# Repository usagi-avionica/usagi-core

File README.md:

# Usagi Core

Flight computer core board by **Usagi Avionica**. An STM32G474 with on-board flash logging, CAN, USB-C and connectors for expansion boards, on a 50 × 50 mm four-layer board designed to be stacked.

## Features

- **MCU:** STM32G474RE (Arm Cortex-M4F, 170 MHz), 24 MHz crystal, 32.768 kHz RTC
- **Storage:** 256 Mbit (32 MB) SPI NOR flash (Infineon S25FL256L)
- **CAN:** classic CAN up to 1 Mbit/s (TI SN65HVD231Q), split termination on board, ESD protection
- **USB:** USB-C, ESD protected; can also power the board through a jumper for debug
- **Power:** 5 V input or USB into a 3.3 V / 1.2 A LDO
- **Expansion:** I2C, SPI, an 8-pin GPIO/ADC connector and 13 GPIO solder pads on the bottom side
- **Feedback:** buzzer, status LED, power indicator LEDs
- **Connectors:** Molex Micro-Lock Plus 1.25 mm with positive locks

## Specifications

| | |
|---|---|
| Board size | 50 × 50 mm |
| Mounting | 4 × M3, 3.5 mm from each corner (43 × 43 mm pattern) |
| Layers | 4, 1.6 mm, ENIG |
| Input voltage | 5 V nominal, **5.5 V maximum** |
| Logic level | 3.3 V |

## Connectors

All board-to-wire connectors are Molex Micro-Lock Plus 1.25 mm right-angle headers (220098 series). Mating housing: Molex 204532 series.

### J6: Power input

| Pin | Signal |
|---|---|
| 1 | VIN (5 V nominal, 5.5 V max) |
| 2 | GND |

### J3: CAN

| Pin | Signal |
|---|---|
| 1 | CANL |
| 2 | CANH |
| 3 | GND |

Split termination (2 × 60.4 Ω + 4.7 nF) is fitted on the board.

### J4: I2C (I2C3)

| Pin | Signal |
|---|---|
| 1 | SCL |
| 2 | SDA |
| 3 | GND |

1.8 kΩ pull-ups to 3.3 V on board.

### J5: SPI (SPI2)

| Pin | Signal |
|---|---|
| 1 | SCK |
| 2 | MISO |
| 3 | MOSI |
| 4 | GND |

There are no chip-select lines on this connector. Use pins from J7 or the solder pads for chip selects. Each SPI device should pull its own CS line up, so it stays deselected while the MCU is in reset.

### J2: Debug

| Pin | Signal |
|---|---|
| 1 | 3.3 V (VTref, reference only; does not power the board) |
| 2 | SWDIO |
| 3 | SWCLK |
| 4 | SWO |
| 5 | UART TX (USART2, from the MCU) |
| 6 | UART RX (USART2, to the MCU) |
| 7 | NRST |
| 8 | GND |

### J7: GPIO / ADC

| Pin | MCU pin | ADC channel |
|---|---|---|
| 1 | PC4 | ADC2_IN5 |
| 2 | PC5 | ADC2_IN11 |
| 3 | PC2 | ADC12_IN8 |
| 4 | PC1 | ADC12_IN7 |
| 5 | PC0 | ADC12_IN6 |
| 6 | PA8 | ADC5_IN1 |
| 7 | PB12 | ADC1_IN11 / ADC4_IN3 |
| 8 | PB11 | ADC12_IN14 |

Every pin can be a GPIO or an ADC input, and each uses a different EXTI line, so all eight can be interrupts at the same time. This connector has no ground pin; each daughter board takes its ground from its power or CAN connection.

> [!WARNING]
> J7 has **no ESD protection or filtering**. Keep signals between 0 and 3.3 V. In analog mode none of these pins are 5 V tolerant.

### GPIO solder pads (bottom side)

The remaining free GPIOs are on solder pads on the bottom of the board, labelled on the silkscreen:

PA10, PA15, PB4, PB7, PB9, PB10, PC6, PC7, PC10, PC11, PC12, PC13, PD2

These pads are unprotected and meant for development and bodge wires. Secure any wire that stays on in flight. PC13 can only source or sink a few mA, so use it only for slow signals.

### J1: USB-C

USB 2.0 full-speed device. It powers the board only when the USB EN jumper is fitted.

## Power

The board runs from J6 (5 V) or USB. The two are diode-ORed (Schottky) into a 3.3 V LDO, so both can be connected at once.

| Jumper | Function |
|---|---|
| USB EN | Fitted: USB powers the board. Removed: USB carries data only. |

| LED | Meaning |
|---|---|
| PWR IN | External power (J6) present |
| USB PWR | USB power present (J21 fitted) |
| 3.3V | 3.3 V rail on |
| STATE | Status LED, driven by firmware |

## Programming

- **SWD** through J2 with any Arm debug probe (ST-LINK, J-Link, etc.).
- **USB DFU bootloader:** set the **BOOT0** switch (SW1) to the BOOT0 position and reset the board. It should then show up on USB as an ST DFU device (STM32CubeProgrammer or `dfu-util`).

## Manufacturing

Designed in **KiCad 10**. The project includes design rules (`usagi-core.kicad_dru`) for PCBWay's standard 4-layer service.

## Releases

Releases are built automatically by GitHub Actions. When a change merged to `main` comes with a new board revision, the workflow:

1. Runs ERC and DRC (errors block the release)
2. Generates the outputs below
3. Publishes a release named **Revision X** with everything in one `release.zip`

| File | Contents |
|---|---|
| `gerber.zip` | Gerbers and drill files, ready to upload to a board house |
| `odb++.zip` | ODB++ fabrication data |
| `schematic.pdf` | Schematic |
| `pcb.pdf` | Copper, mask and fabrication layers |
| `bom.csv` | Bill of materials, grouped by manufacturer part number |
| `ibom.html` | Interactive BOM for assembly |
| `netlist.net` | Netlist |
| `isometric_top.png`, `isometric_bottom.png` | 3D renders |
| `erc.rpt`, `drc.rpt` | Check reports |

**To publish a new revision:** change the Revision field in the Page Settings of both the schematic and the PCB (e.g. `A` → `B`), then merge to `main`. Merges that don't change the revision don't produce a release.

## License

Hardware licensed under **CERN-OHL-S**. See [LICENSE](LICENSE).

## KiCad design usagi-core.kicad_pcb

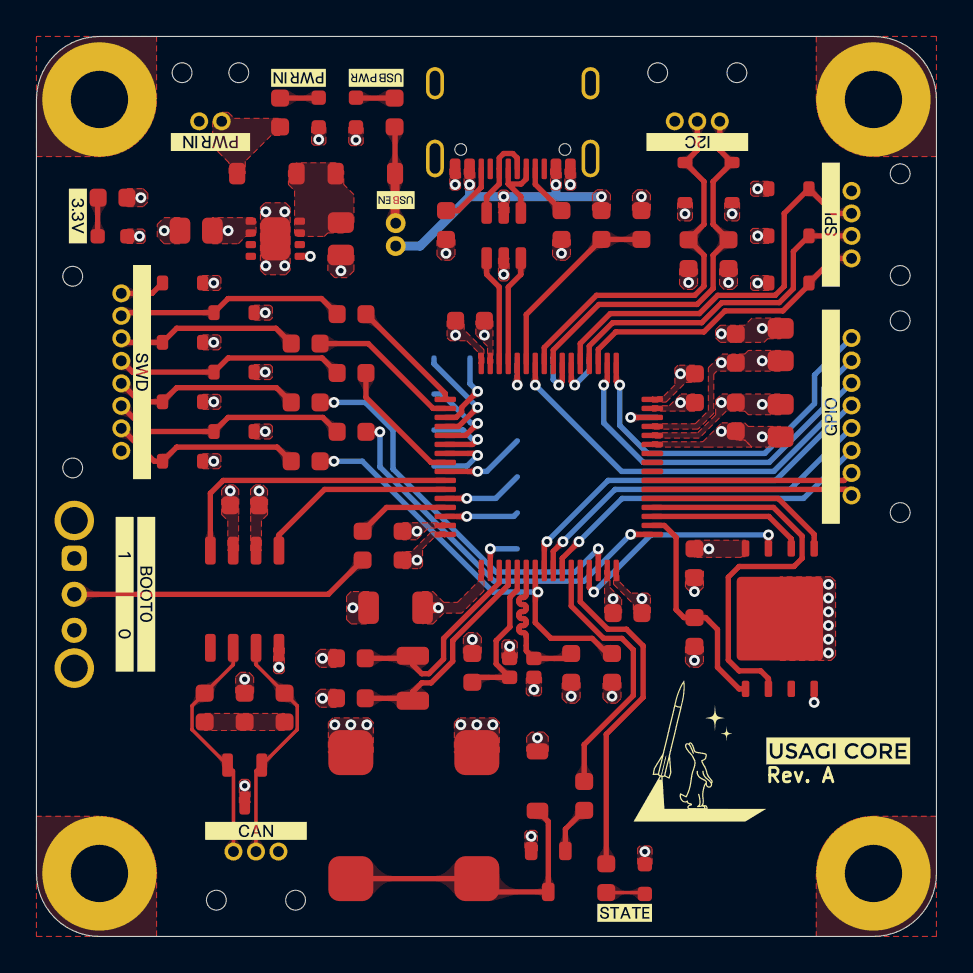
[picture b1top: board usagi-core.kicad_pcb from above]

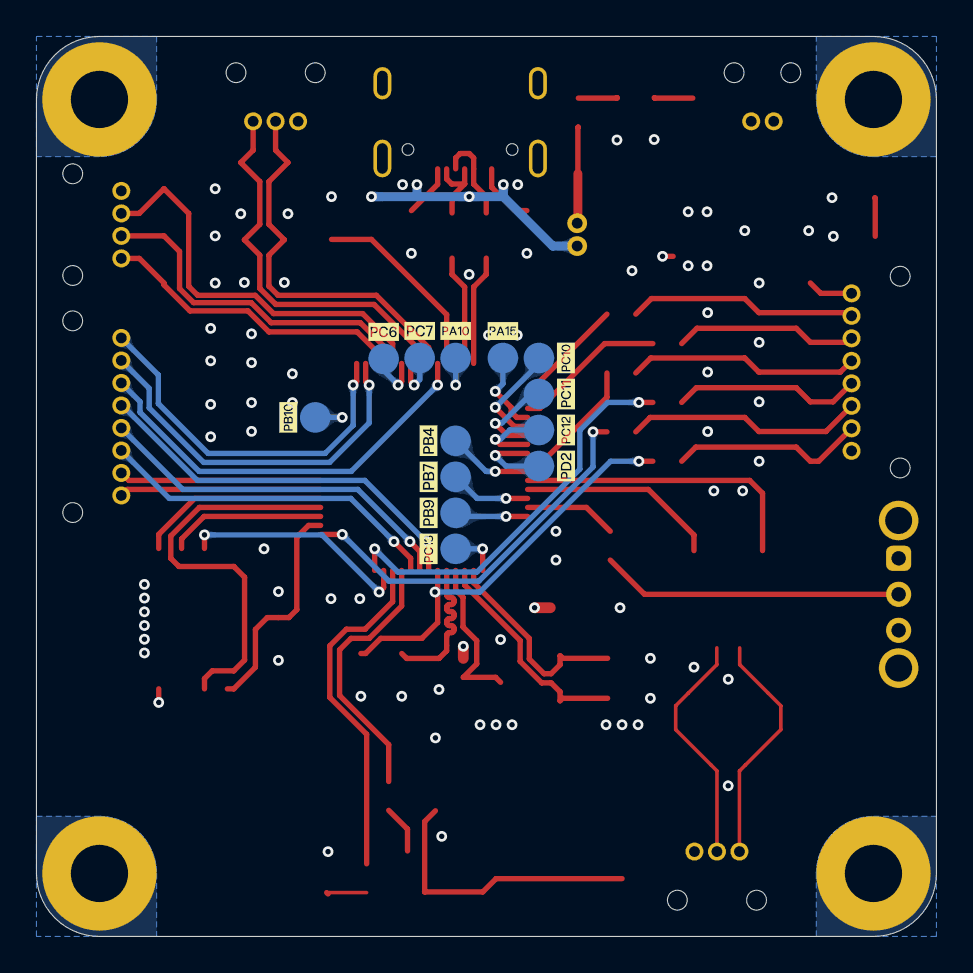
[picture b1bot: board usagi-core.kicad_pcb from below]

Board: 4 copper layers, 50.0 x 50.0 mm, 123 parts (26 on the bottom side), 75 nets.

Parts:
BZ1: CMT-8540S-SMT-TR
C1, C2, C3, C4, C8, C10, C15, C17: 100nF; C_0603_Density_Nominal
C5: 4.7μF; C_1206_Density_Nominal
C6: 10nF; C_0603_Density_Nominal
C7, C9, C18: 1μF; C_0805_Density_Nominal
C11, C12: 6.8pF; C_0603_Density_Nominal
C13, C14: 5.1pF; C_0603_Density_Nominal
C16: 4.7nF; C_0603_Density_Nominal
C19: 10μF; C_0805_Density_Nominal
D1, D15, D18, D19: Green; SML-D12P8WT86C
D2, D3, D4, D5, D6, D7, D8, D9, D10, D11, D12, D13: SZESD7351HT1G
D14, D16, D17: STPS140ZY
J1: USB4105-GF-A-120
J2, J7: 2200980871
J3, J4: 2200980371
J5: 2200980471
J6: 2200980271
J8, J9, J10, J11, J12, J13, J14, J15, J16, J17, J18, J19, J20: SolderPad
J21: M50-3530242
MH1, MH2, MH3, MH4: M3
Q1: SMMBT2222ALT1G
R1, R2: 1.8kΩ; R_0603_Density_Nominal
R3, R8: 10kΩ; R_0603_Density_Nominal
R4, R5: 5.1kΩ; R_0603_Density_Nominal
R6: 82kΩ; R_0603_Density_Nominal
R7: 33kΩ; R_0603_Density_Nominal
R9, R10: 60.4Ω; R_0603_Density_Nominal
R11, R21: 100Ω; R_0603_Density_Nominal
R12, R13, R14, R15, R16, R17: 49.9Ω; R_0603_Density_Nominal
R18, R19, R20: 220Ω; R_0603_Density_Nominal
SW1: OS102011MA1QN1
U1: STM32G474RET3
U2: USBLC6-2SC6
U3: S25FL256LAGNFM010
U4: SN65HVD231QDRG4Q1
U5: ESD2CAN24DBZRQ1
U6: NCV8187AMLE330TCG
Y1: 24MHz; CS10820-24M
Y2: 32.768kHz; MU00525-32.768K
kibuzzard-6AF2C97C: G***; kibuzzard-6AF2C97C
kibuzzard-6AF2CA52: G***; kibuzzard-6AF2CA52
kibuzzard-6AF2CCF0: G***; kibuzzard-6AF2CCF0
kibuzzard-6AF3A4A3: G***; kibuzzard-6AF3A4A3
kibuzzard-6AF3A46B: G***; kibuzzard-6AF3A46B
kibuzzard-6AF3A47A: G***; kibuzzard-6AF3A47A
kibuzzard-6AF3A482: G***; kibuzzard-6AF3A482
kibuzzard-6AF3A495: G***; kibuzzard-6AF3A495
kibuzzard-6AF5A14A: G***; kibuzzard-6AF5A14A
kibuzzard-6AF5D7C2: G***; kibuzzard-6AF5D7C2
kibuzzard-6AF578D1: G***; kibuzzard-6AF578D1
kibuzzard-6AF578DA: G***; kibuzzard-6AF578DA
kibuzzard-6AF578E0: G***; kibuzzard-6AF578E0
kibuzzard-6AF578EA: G***; kibuzzard-6AF578EA
kibuzzard-6AF1947B: G***; kibuzzard-6AF1947B
kibuzzard-6AF1962F: G***; kibuzzard-6AF1962F
kibuzzard-6AF4418B: G***; kibuzzard-6AF4418B
kibuzzard-6AF5783D: G***; kibuzzard-6AF5783D
kibuzzard-6AF5791D: G***; kibuzzard-6AF5791D
kibuzzard-6AF5792A: G***; kibuzzard-6AF5792A
kibuzzard-6AF5796A: G***; kibuzzard-6AF5796A
kibuzzard-6AF19634: G***; kibuzzard-6AF19634
kibuzzard-6AF44698: G***; kibuzzard-6AF44698
kibuzzard-6AF57785: G***; kibuzzard-6AF57785
kibuzzard-6AF57819: G***; kibuzzard-6AF57819
kibuzzard-6AF57844: G***; kibuzzard-6AF57844
kibuzzard-6AF57915: G***; kibuzzard-6AF57915
kibuzzard-6AF57924: G***; kibuzzard-6AF57924

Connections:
+3.3V: BZ1.1 (+), C1.1, C2.1, C3.1, C4.1, C5.1, C6.1, C7.1, C8.1, C9.1, C15.1, C17.1, C19.1, D2.1, D14.1, J2.1, R1.1, R2.1, R8.1, R21.1, SW1.1, U1.1 (VBAT), U1.16 (VDD), U1.28 (VREF+), U1.29 (VDDA), U1.32 (VDD), U1.48 (VDD), U1.64 (VDD), U3.8 (VCC), U4.3 (VCC), U6.1 (OUT), U6.2 (SNS)
/CAN_N: J3.1, R10.2, U4.6 (CANL), U5.2 (I/O2)
/CAN_P: J3.2, R9.1, U4.7 (CANH), U5.1 (I/O1)
/MCU_BOOT0: R3.1, U1.61 (BOOT0)
/MCU_HSE_IN: C11.1, U1.5 (OSC_IN), Y1.1
/MCU_HSE_OUT: C12.1, U1.6 (OSC_OUT), Y1.3
/MCU_LED: R11.1, U1.12 (PA0)
/MCU_LSE_IN: C13.1, U1.3 (OSC32_IN), Y2.1
/MCU_LSE_OUT: C14.1, U1.4 (OSC32_OUT), Y2.2
/USB_CONN_CC1: J1.A5 (CC1), R5.1
/USB_CONN_CC2: J1.B5 (CC2), R4.1
/USB_CONN_D+: J1.A6 (DP1), J1.B6 (DP2), U2.6 (I/O1)
/USB_CONN_D-: J1.A7 (DN1), J1.B7 (DN2), U2.4 (I/O2)
GND: C1.2, C2.2, C3.2, C4.2, C5.2, C6.2, C7.2, C8.2, C9.2, C10.2, C11.2, C12.2, C13.2, C14.2, C15.2, C16.2, C17.2, C18.2, C19.2, D1.1, D2.2, D3.2, D4.2, D5.2, D6.2, D7.2, D8.2, D9.2, D10.2, D11.2, D12.2, D13.2, D15.1, D18.1, D19.1, J1.A1 (GND), J1.A12 (GND), J1.B1 (GND), J1.B12 (GND), J1.SH, J2.8, J3.3, J4.3, J5.4, J6.2, Q1.2 (E), R4.2, R5.2, R7.2, SW1.3, U1.15 (VSS), U1.27 (VSSA), U1.31 (VSS), U1.47 (VSS), U1.63 (VSS), U2.2 (GND), U3.4 (VSS), U3.9 (EP), U4.2 (GND), U4.8 (RS), U5.3 (GND), U6.5 (GND), U6.9 (GND), Y1.2 (GND), Y1.4 (GND)
MCU_BUZZER: R18.1, U1.11 (PC3)
MCU_CAN2_RX: U1.58 (FDCAN2_RX), U4.4 (R)
MCU_CAN2_TX: U1.59 (FDCAN2_TX), U4.1 (D)
MCU_I2C3_SCL: D10.1, J4.1, R1.2, U1.40 (I2C3_SCL)
MCU_I2C3_SDA: D9.1, J4.2, R2.2, U1.41 (I2C3_SDA)
MCU_MEM_CS: R8.2, U1.18 (PA4), U3.1 (CS)
MCU_MEM_NRST: U1.13 (PA1), U3.7 (~RESET)
MCU_NRST: C10.1, R15.1, U1.7 (NRST)
MCU_SPI1_MISO: U1.20 (SPI1_MISO), U3.2 (SO)
MCU_SPI1_MOSI: U1.21 (SPI1_MOSI), U3.5 (SI)
MCU_SPI1_SCK: U1.19 (SPI1_SCK), U3.6 (SCK)
MCU_SPI2_MISO: D12.1, J5.2, U1.36 (SPI2_MISO)
MCU_SPI2_MOSI: D11.1, J5.3, U1.37 (SPI2_MOSI)
MCU_SPI2_SCK: D13.1, J5.1, U1.35 (SPI2_SCK)
MCU_SWCLK: R13.1, U1.50 (SWCLK-JTCK)
MCU_SWDIO: R12.1, U1.49 (SWDIO-JTMS)
MCU_SWO: R14.1, U1.56 (JTDO-TRACESWO)
MCU_USART2_RX: R16.1, U1.17 (USART2_RX)
MCU_USART2_TX: R17.1, U1.14 (USART2_TX)
MCU_USB_D+: U1.46 (USB_DP), U2.1 (I/O1)
MCU_USB_D-: U1.45 (USB_DM), U2.3 (I/O2)
MCU_USB_VUSB: R6.2, R7.1, U1.43 (PA9)
unnamed: BZ1.2 (-), D14.2, Q1.3 (C)
unnamed: C16.1, R9.2, R10.1
unnamed: D1.2, R11.2
unnamed: D3.1, J2.2, R12.2
unnamed: D4.1, J2.3, R13.2
unnamed: D5.1, J2.4, R14.2
unnamed: D6.1, J2.5, R17.2
unnamed: D7.1, J2.6, R16.2
unnamed: D8.1, J2.7, R15.2
unnamed: D15.2, R19.2
unnamed: D16.2, J6.1, R20.1
unnamed: D17.2, J21.2, R19.1
unnamed: D18.2, R20.2
unnamed: D19.2, R21.2
unnamed: Q1.1 (B), R18.2
unnamed: R3.2, SW1.2
unnamed: C18.1, D16.1, D17.1, U6.7 (EN), U6.8 (IN)
PA8: J7.6, U1.42 (PA8)
PA10: J8.1 (1_1), U1.44 (PA10)
PA15: J20.1 (1_1), U1.51 (PA15)
PB4: J15.1 (1_1), U1.57 (PB4)
PB7: J14.1 (1_1), U1.60 (PB7)
PB9: J13.1 (1_1), U1.62 (PB9)
PB10: J11.1 (1_1), U1.30 (PB10)
PB11: J7.8, U1.33 (PB11)
PB12: J7.7, U1.34 (PB12)
PC0: J7.5, U1.8 (PC0)
PC1: J7.4, U1.9 (PC1)
PC2: J7.3, U1.10 (PC2)
PC4: J7.1, U1.22 (PC4)
PC5: J7.2, U1.23 (PC5)
PC6: J10.1 (1_1), U1.38 (PC6)
PC7: J9.1 (1_1), U1.39 (PC7)
PC10: J19.1 (1_1), U1.52 (PC10)
PC11: J18.1 (1_1), U1.53 (PC11)
PC12: J17.1 (1_1), U1.54 (PC12)
PC13: J12.1 (1_1), U1.2 (PC13)
PD2: J16.1 (1_1), U1.55 (PD2)
VUSB: J1.A4 (VBUS), J1.A9 (VBUS), J1.B4 (VBUS), J1.B9 (VBUS), J21.1, R6.1, U2.5 (VBUS)

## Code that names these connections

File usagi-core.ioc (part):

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Mcu.Name=STM32G474R(B-C-E)Tx
Mcu.Package=LQFP64
Mcu.UserName=STM32G474RETx
PA0.GPIOParameters=GPIO_Label
PA0.GPIO_Label=MCU_LED
PA0.Signal=GPIO_Output
PA1.GPIOParameters=GPIO_Label
PA1.GPIO_Label=MCU_MEM_NRST
PA1.Signal=GPIO_Output
PA11.Mode=Device
PA11.Signal=USB_DM
PA12.Mode=Device
PA12.Signal=USB_DP
PA13.Mode=Trace_Asynchronous_SW
PA13.Signal=SYS_JTMS-SWDIO
PA14.Mode=Trace_Asynchronous_SW
PA14.Signal=SYS_JTCK-SWCLK
PA2.Mode=Asynchronous
PA2.Signal=USART2_TX
PA3.Mode=Asynchronous
PA3.Signal=USART2_RX
PA4.GPIOParameters=GPIO_Label
PA4.GPIO_Label=MCU_MEM_CS
PA4.Signal=GPIO_Output
PA5.Mode=Full_Duplex_Master
PA5.Signal=SPI1_SCK
PA6.Mode=Full_Duplex_Master
PA6.Signal=SPI1_MISO
PA7.Mode=Full_Duplex_Master
PA7.Signal=SPI1_MOSI
PA9.GPIOParameters=GPIO_Label
PA9.GPIO_Label=USB_VBUS
PA9.Signal=GPIO_Input
PB13.Mode=Full_Duplex_Master
PB13.Signal=SPI2_SCK
PB14.Mode=Full_Duplex_Master
PB14.Signal=SPI2_MISO
PB15.Mode=Full_Duplex_Master
PB15.Signal=SPI2_MOSI
PB3.Mode=Trace_Asynchronous_SW
PB3.Signal=SYS_JTDO-SWO
PB5.Mode=FDCAN_Activate
PB5.Signal=FDCAN2_RX
PB6.Mode=FDCAN_Activate
PB6.Signal=FDCAN2_TX
PC14-OSC32_IN.Mode=LSE-External-Oscillator
PC14-OSC32_IN.Signal=RCC_OSC32_IN
PC15-OSC32_OUT.Mode=LSE-External-Oscillator
PC15-OSC32_OUT.Signal=RCC_OSC32_OUT
PC3.Signal=S_TIM1_CH4
PC8.Mode=I2C
PC8.Signal=I2C3_SCL
PC9.Mode=I2C
PC9.Signal=I2C3_SDA
PF0-OSC_IN.Mode=HSE-External-Oscillator
PF0-OSC_IN.Signal=RCC_OSC_IN
PF1-OSC_OUT.Mode=HSE-External-Oscillator
PF1-OSC_OUT.Signal=RCC_OSC_OUT
RCC.HSE_VALUE=24000000
RCC.SYSCLKFreq_VALUE=170000000
RCC.SYSCLKSource=RCC_SYSCLKSOURCE_PLLCLK
board=custom

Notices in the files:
parts and their libraries:
LICENSE: CERN-OHL-S
